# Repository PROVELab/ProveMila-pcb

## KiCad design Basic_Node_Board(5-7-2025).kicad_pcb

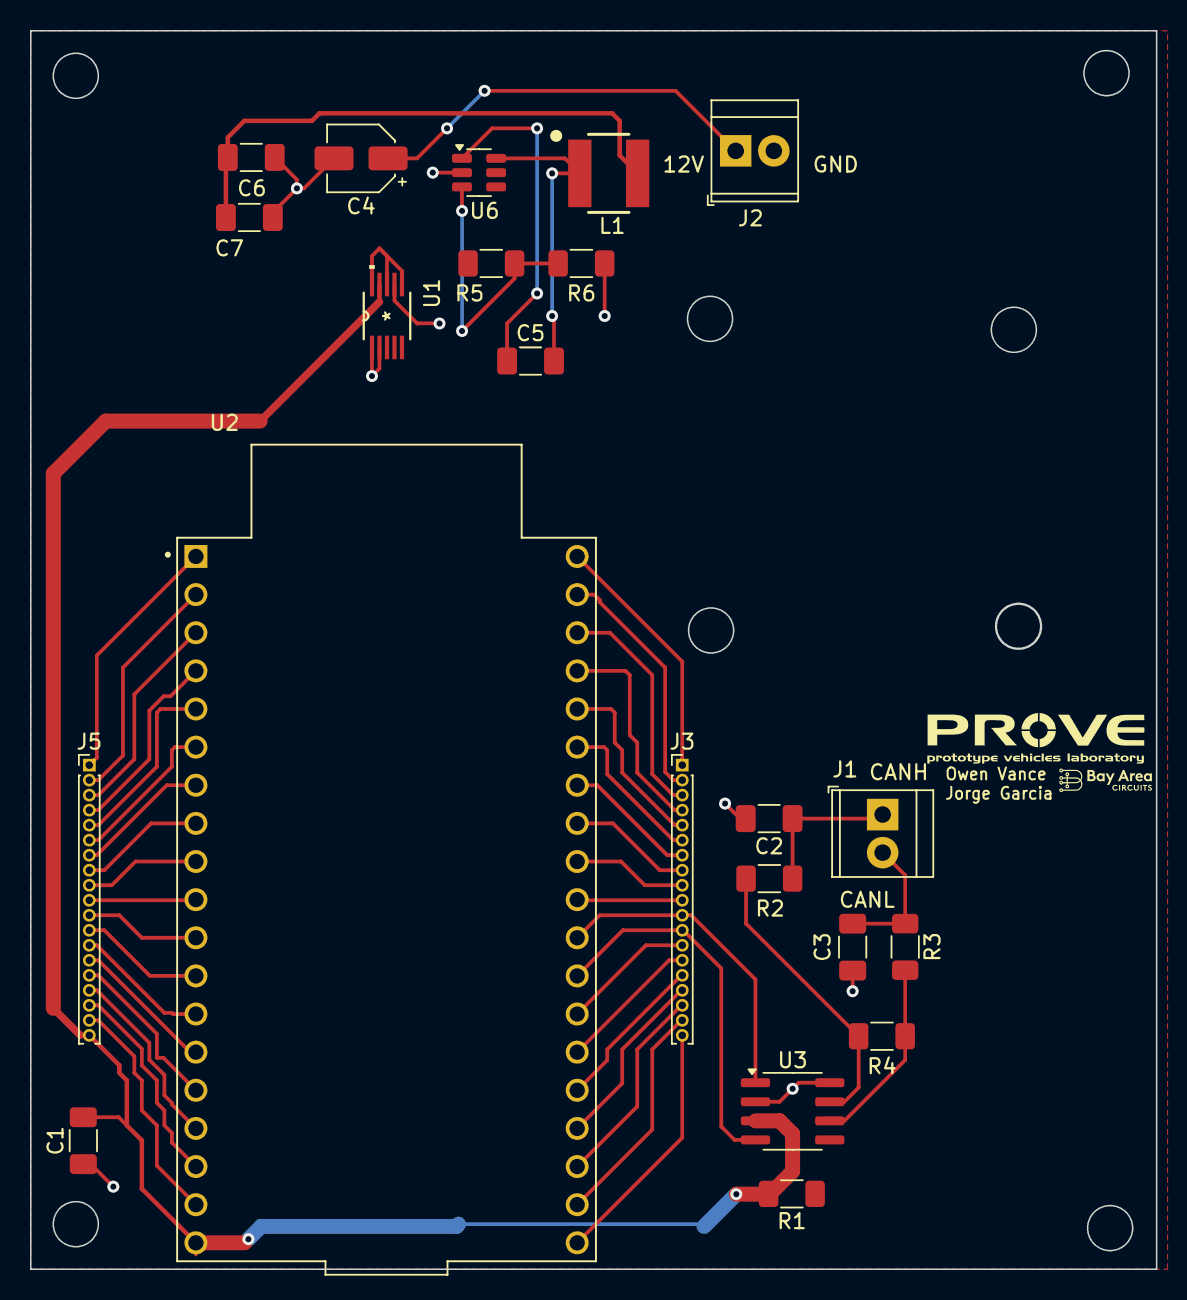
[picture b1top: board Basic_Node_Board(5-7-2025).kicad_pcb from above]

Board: 2 copper layers, 75.0 x 82.5 mm, 22 parts (0 on the bottom side), 48 nets.

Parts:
C1, C5: 0.1u; C_1206_3216Metric_Pad1.33x1.80mm_HandSolder
C2, C3: 30p; C_1206_3216Metric_Pad1.33x1.80mm_HandSolder
C4: 2.2u; CP_Elec_4x5.4
C6, C7: 10u; C_1206_3216Metric_Pad1.33x1.80mm_HandSolder
J1: Conn_01x02_Pin; TerminalBlock_TE_282834-2_1x02_P2.54mm_Horizontal
J2: Conn_01x02; TerminalBlock_TE_282834-2_1x02_P2.54mm_Horizontal
J3, J5: Conn_01x19_Socket; PinHeader_1x19_P1.00mm_Vertical
L1: 10u; WE-LQS_5040
R1: 30m; R_1206_3216Metric_Pad1.30x1.75mm_HandSolder
R2, R3: 0; R_1206_3216Metric_Pad1.30x1.75mm_HandSolder
R4: 120; R_1206_3216Metric_Pad1.30x1.75mm_HandSolder
R5: 115k; R_1206_3216Metric_Pad1.30x1.75mm_HandSolder
R6: 22.1k; R_1206_3216Metric_Pad1.30x1.75mm_HandSolder
U1: INA220 Current Monitor; DGS10
U2: ESP32-DEVKIT-C; MODULE_ESP32-DEVKITC
U3: TJA1050T/CM,118; SOIC-8_3.9x4.9mm_P1.27mm
U6: AP64060WU-7; TSOT-23-6

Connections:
+5V: R1.1, R5.1, U1.6 (VS), U1.8 (VBUS), U1.10 (VIN+)
+5VD: C1.2, J5.19, R1.2, U1.9 (VIN-), U2.19 (EXT_5V), U3.3 (VCC)
/Microcontroller/BUCK_5V: C6.1, C7.1, L1.2
/Microcontroller/CANH: C2.1, J1.1, R2.1
/Microcontroller/CANL: C3.1, J1.2, R3.1
/Power_Supply/12V_IN: C4.1, J2.1
GND: C1.1, C2.2, C3.2, C4.2, C6.2, C7.2, J2.2, J5.14, R6.2, U1.1 (A1), U1.2 (A0), U1.7 (GND), U2.14 (GND1), U3.2 (GND), U3.8 (S), U6.2 (GND)
unnamed: J3.1, U2.38 (GND3)
unnamed: J3.2, U2.37 (IO23)
unnamed: J3.3, U2.36 (IO22)
unnamed: J3.4, U2.35 (TXD0)
unnamed: J3.5, U2.34 (RXD0)
unnamed: J3.6, U2.33 (IO21)
unnamed: J3.7, U2.32 (GND2)
unnamed: J3.8, U2.31 (IO19)
unnamed: J3.9, U2.30 (IO18)
unnamed: J3.10, U2.29 (IO5)
unnamed: J3.11, U2.28 (IO17), U3.1 (TXD)
unnamed: J3.12, U2.27 (IO16), U3.4 (RXD)
unnamed: J3.13, U2.26 (IO4)
unnamed: J3.14, U2.25 (IO0)
unnamed: J3.15, U2.24 (IO2)
unnamed: J3.16, U2.23 (IO15)
unnamed: J3.17, U2.22 (SD1)
unnamed: J3.18, U2.21 (SD0)
unnamed: J3.19, U2.20 (CLK)
unnamed: J5.1, U2.1 (3V3)
unnamed: J5.2, U2.2 (EN)
unnamed: J5.3, U2.3 (SENSOR_VP)
unnamed: J5.4, U2.4 (SENSOR_VN)
unnamed: J5.5, U2.5 (IO34)
unnamed: J5.6, U2.6 (IO35)
unnamed: J5.7, U2.7 (IO32)
unnamed: J5.8, U2.8 (IO33)
unnamed: J5.9, U2.9 (IO25)
unnamed: J5.10, U2.10 (IO26)
unnamed: J5.11, U2.11 (IO27)
unnamed: J5.12, U2.12 (IO14)
unnamed: J5.13, U2.13 (IO12)
unnamed: J5.15, U2.15 (IO13)
unnamed: J5.16, U2.16 (SD2)
unnamed: J5.17, U2.17 (SD3)
unnamed: J5.18, U2.18 (CMD)
unnamed: R2.2, R4.1, U3.7 (CANH)
unnamed: R3.2, R4.2, U3.6 (CANL)
unnamed: C5.1, U6.1 (BST)
unnamed: R5.2, R6.1, U6.3 (FB)
unnamed: C5.2, L1.1, U6.6 (SW)

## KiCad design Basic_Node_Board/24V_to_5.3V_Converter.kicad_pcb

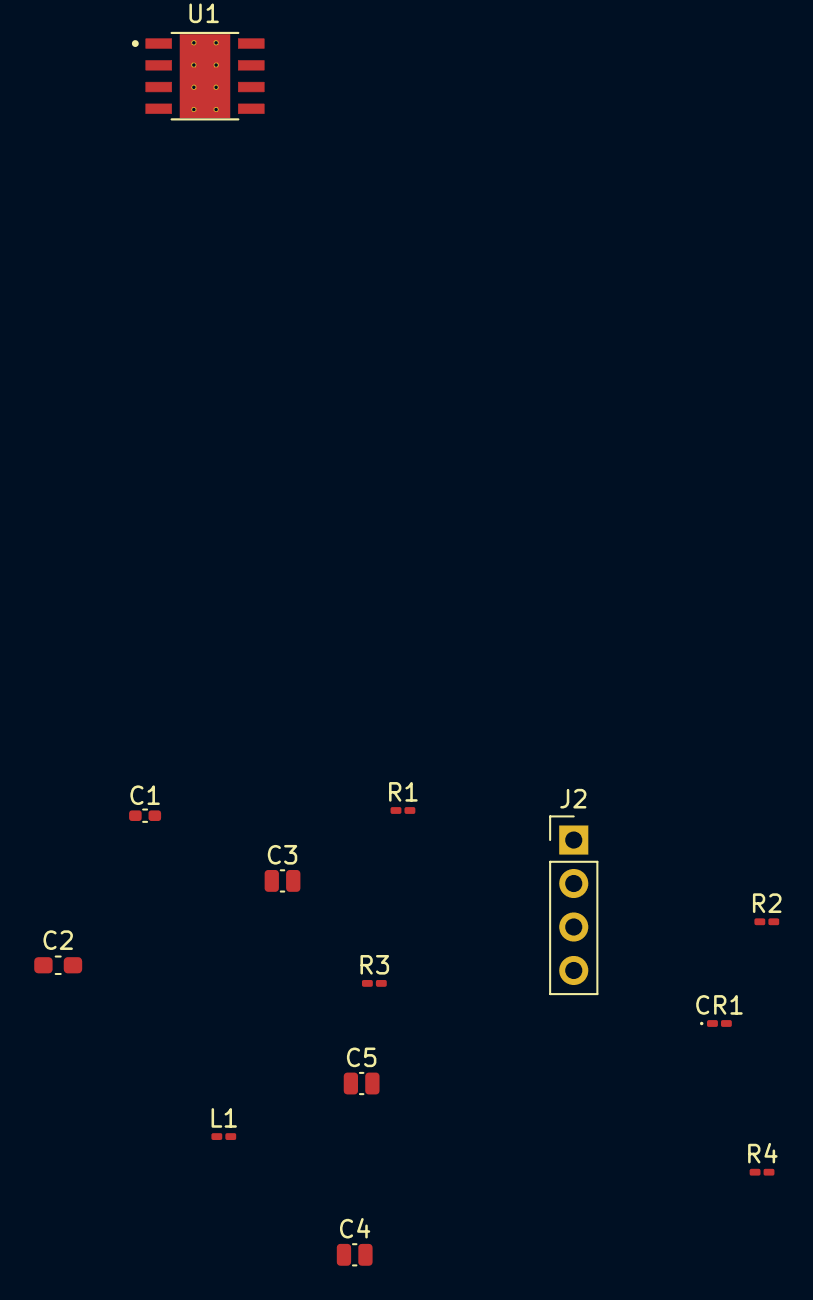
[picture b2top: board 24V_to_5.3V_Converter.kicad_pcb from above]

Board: 2 copper layers, 13 parts (0 on the bottom side), 9 nets, no tracks yet.

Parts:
C1: 10TPE47MAZB; C_0402_1005Metric_Pad0.74x0.62mm_HandSolder
C2: CL05C110JB5NNNC; C_0603_1608Metric_Pad1.08x0.95mm_HandSolder
C3: C0805C122J5GACTU; C_0504_1310Metric_Pad0.83x1.28mm_HandSolder
C4: GRM31CR71H475KA12L; C_0504_1310Metric_Pad0.83x1.28mm_HandSolder
C5: 08053C104KAT2A; C_0504_1310Metric_Pad0.83x1.28mm_HandSolder
CR1: B560C-13-F; D_0201_0603Metric_Pad0.64x0.40mm_HandSolder
J2: Conn_01x02; PinHeader_1x04_P2.54mm_Vertical
L1: SRN8040-100M; L_0201_0603Metric_Pad0.64x0.40mm_HandSolder
R1: CRCW040261K9FKED; R_0201_0603Metric_Pad0.64x0.40mm_HandSolder
R2: CRCW040211K0FKED; R_0201_0603Metric_Pad0.64x0.40mm_HandSolder
R3: CRCW0402118KFKED; R_0201_0603Metric_Pad0.64x0.40mm_HandSolder
R4: RC0201FR-0723K7L; R_0201_0603Metric_Pad0.64x0.40mm_HandSolder
U1: TPS54560BQDDARQ1; VREG_LM5017MR_NOPB

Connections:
5.3V OUT: C1.1, L1.1, R1.1
/24V: C4.2, J2.1, U1.2 (VIN)
GND: C1.2, C2.2, C3.1, C4.1, CR1.2, J2.2, R2.1, R3.1, U1.7 (GND)
unnamed: C3.2, R4.1
unnamed: C5.2, U1.1 (BOOT)
unnamed: C2.1, R4.2, U1.6 (COMP)
unnamed: R1.2, R2.2, U1.5 (FB)
unnamed: R3.2, U1.4 (RT/CLK)
unnamed: C5.1, CR1.1, L1.2, U1.8 (SW)

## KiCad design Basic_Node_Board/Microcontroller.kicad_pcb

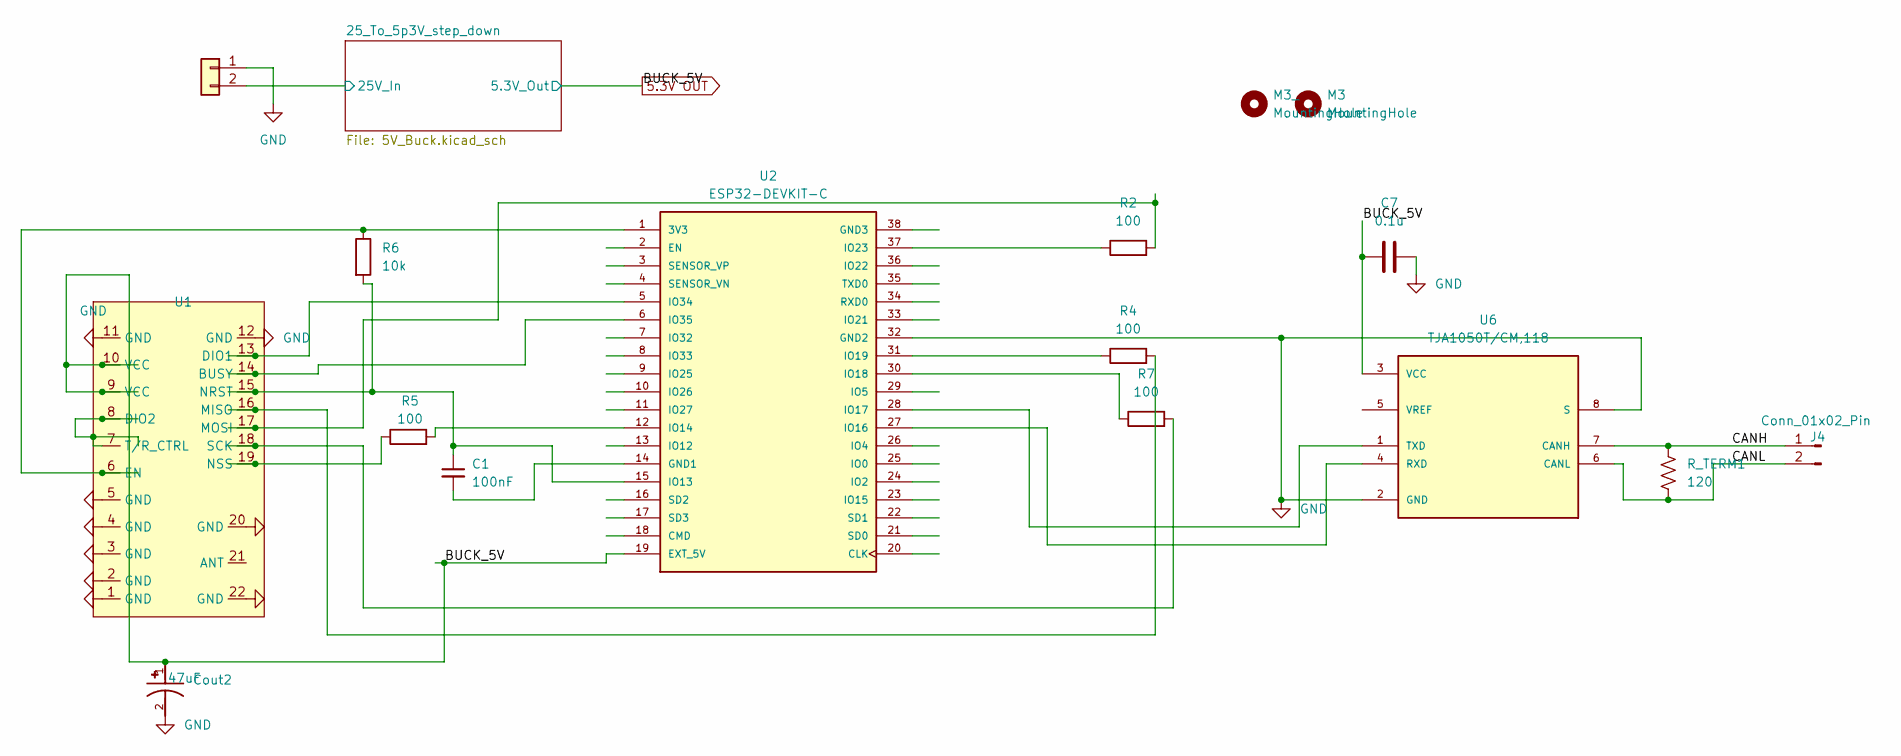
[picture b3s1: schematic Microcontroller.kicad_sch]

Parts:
C1: 100nF; C_1206_3216Metric_Pad1.33x1.80mm_HandSolder
C7: 0.1u; C_1206_3216Metric_Pad1.33x1.80mm_HandSolder; MPN 1206B104K500CT
Cout2: 47uF; CP_EIA-3528-21_Kemet-B_HandSolder
J1: Conn_01x02; TE_1877285-2
J4: Conn_01x02_Pin; TE_1877285-2
M3, M3_: MountingHole; MountingHole_3.2mm_M3
R2, R4, R5, R7: 100; R_1206_3216Metric_Pad1.30x1.75mm_HandSolder
R6: 10k; R_1206_3216Metric_Pad1.30x1.75mm_HandSolder
R_TERM1: 120; R_1206_3216Metric_Pad1.30x1.75mm_HandSolder; MPN RMCF1206JT120R
U1: E22P-915M30S
U2: ESP32-DEVKIT-C; MODULE_ESP32-DEVKITC; PARTREV N/A
U6: TJA1050T/CM,118; SOIC-8_3.9x4.9mm_P1.27mm; PARTREV 4

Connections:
5.3V OUT: C7.2, Cout2.1, U1.9 (VCC), U1.10 (VCC), U2.19 (EXT_5V), U6.3 (VCC); also elsewhere on the board
/25_To_5p3V_step_down/25V_In: J1.2; also elsewhere on the board
/CANH: J4.1, R_TERM1.1, U6.7 (CANH)
/CANL: J4.2, R_TERM1.2, U6.6 (CANL)
GND: C7.1, Cout2.2, J1.1, U1.1 (GND), U1.2 (GND), U1.3 (GND), U1.4 (GND), U1.5 (GND), U1.11 (GND), U1.12 (GND), U1.20 (GND), U1.22 (GND), U2.32 (GND2), U6.2 (GND), U6.8 (S); also elsewhere on the board
unnamed: U1.14 (BUSY), U2.6 (IO35)
unnamed: U1.13 (DIO1), U2.5 (IO34)
unnamed: U1.7 (T/R_CTRL), U1.8 (DIO2)
unnamed: R6.1, U1.6 (EN), U2.1 (3V3)
unnamed: R4.2, U1.16 (MISO)
unnamed: R2.2, U1.17 (MOSI)
unnamed: C1.1, R6.2, U1.15 (NRST), U2.15 (IO13)
unnamed: R5.1, U1.19 (NSS)
unnamed: R7.2, U1.18 (SCK)
unnamed: C1.2, U2.14 (GND1)
unnamed: R5.2, U2.12 (IO14)
unnamed: U2.27 (IO16), U6.4 (RXD)
unnamed: U2.28 (IO17), U6.1 (TXD)
unnamed: R7.1, U2.30 (IO18)
unnamed: R4.1, U2.31 (IO19)
unnamed: R2.1, U2.37 (IO23)

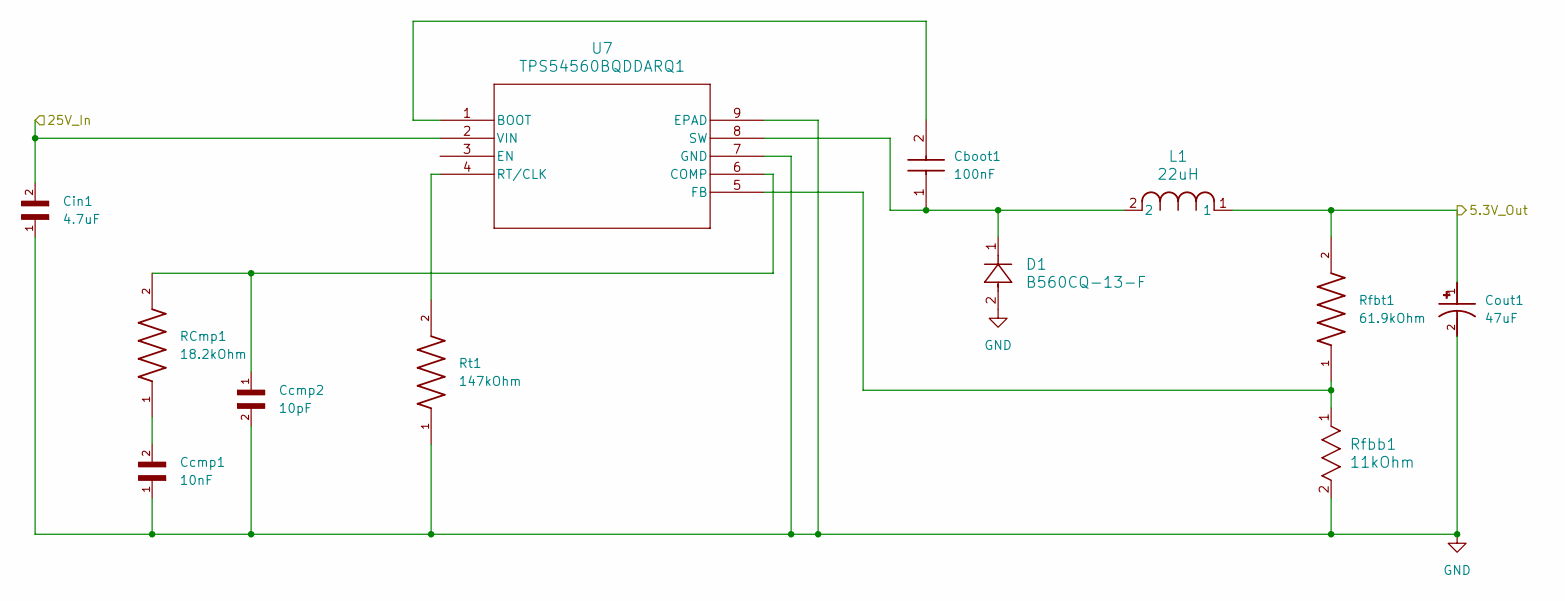
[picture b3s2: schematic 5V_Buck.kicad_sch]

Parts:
Cboot1: 100nF; C_1206_3216Metric_Pad1.33x1.80mm_HandSolder
Ccmp1: 10nF; C_1206_3216Metric_Pad1.33x1.80mm_HandSolder
Ccmp2: 10pF; C_1206_3216Metric_Pad1.33x1.80mm_HandSolder
Cin1: 4.7uF; C_1206_3216Metric_Pad1.33x1.80mm_HandSolder
Cout1: 47uF; CP_EIA-3528-21_Kemet-B_HandSolder
D1: B560CQ-13-F; D_SMC
L1: 22uH; L_Bourns_SRP1245A
RCmp1: 18.2kOhm; R_1206_3216Metric_Pad1.30x1.75mm_HandSolder
Rfbb1: 11kOhm; R_1206_3216Metric_Pad1.30x1.75mm_HandSolder
Rfbt1: 61.9kOhm; R_1206_3216Metric_Pad1.30x1.75mm_HandSolder
Rt1: 147kOhm; R_1206_3216Metric_Pad1.30x1.75mm_HandSolder
U7: TPS54560BQDDARQ1; SOIC-8-1EP_3.9x4.9mm_P1.27mm_EP2.29x3mm

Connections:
5.3V OUT: Cout1.1, L1.1, Rfbt1.2; also elsewhere on the board
/25_To_5p3V_step_down/25V_In: Cin1.2, U7.2 (VIN); also elsewhere on the board
GND: Ccmp1.1, Ccmp2.2, Cin1.1, Cout1.2, D1.2, Rfbb1.2, Rt1.1, U7.7 (GND), U7.9 (EPAD); also elsewhere on the board
unnamed: Ccmp1.2, RCmp1.1
unnamed: Cboot1.2, U7.1 (BOOT)
unnamed: Ccmp2.1, RCmp1.2, U7.6 (COMP)
unnamed: Rfbb1.1, Rfbt1.1, U7.5 (FB)
unnamed: Rt1.2, U7.4 (RT/CLK)
unnamed: Cboot1.1, D1.1, L1.2, U7.8 (SW)

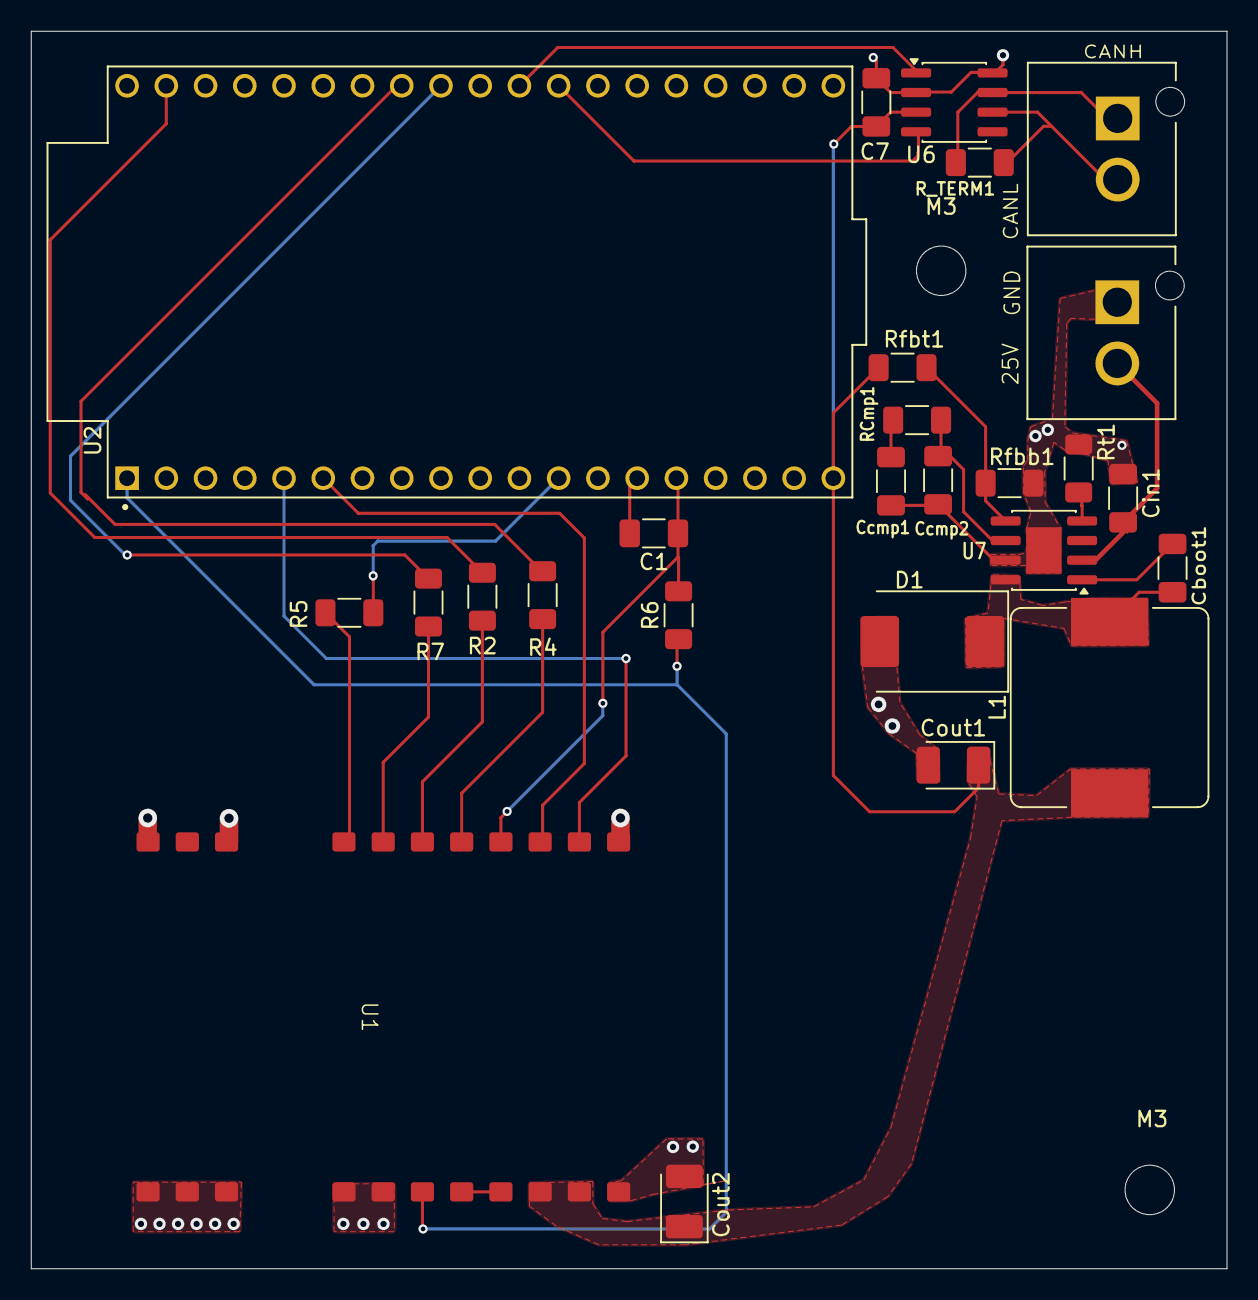
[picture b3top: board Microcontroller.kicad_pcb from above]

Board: 4 copper layers, 77.4 x 80.1 mm, 28 parts (0 on the bottom side), 27 nets.

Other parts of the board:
M3_1: MountingHole; MountingHole_3.2mm_M3

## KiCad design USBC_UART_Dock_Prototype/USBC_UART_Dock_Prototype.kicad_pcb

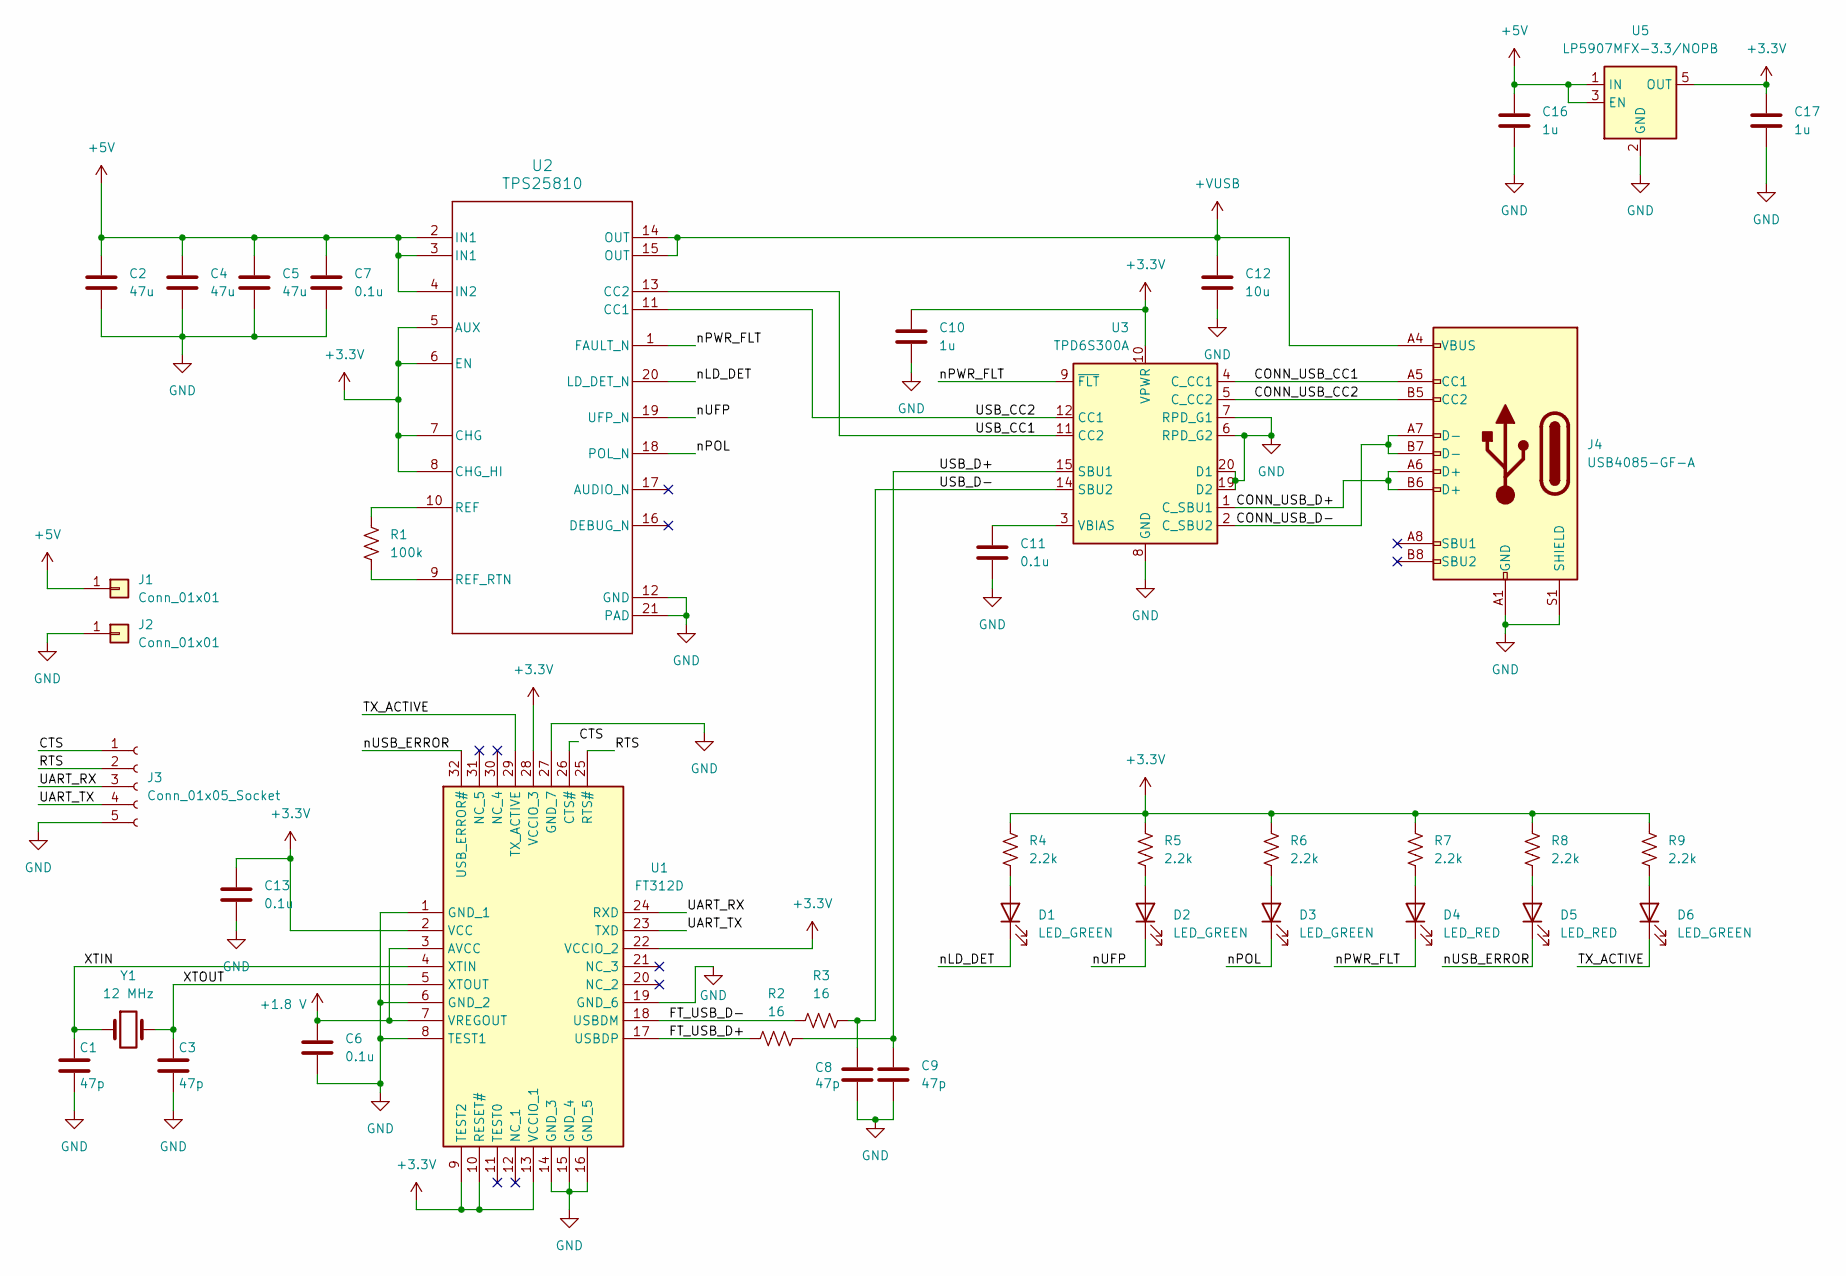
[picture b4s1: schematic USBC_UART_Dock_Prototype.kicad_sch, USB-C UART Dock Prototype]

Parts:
C1, C3, C8, C9: 47p; C_1206_3216Metric_Pad1.33x1.80mm_HandSolder; MPN 885012008003
C2, C4, C5: 47u; C_1206_3216Metric_Pad1.33x1.80mm_HandSolder; MPN CL31A476MQHNNWE
C6, C7, C11, C13: 0.1u; C_0603_1608Metric_Pad1.08x0.95mm_HandSolder; MPN GRM188R71H104KA93D
C10, C16, C17: 1u; C_1206_3216Metric_Pad1.33x1.80mm_HandSolder; MPN 885012208013
C12: 10u; C_1206_3216Metric_Pad1.33x1.80mm_HandSolder; MPN CL31A106KPHNNNE
D1, D2, D3, D6: LED_GREEN; LED_0805_2012Metric_Pad1.15x1.40mm_HandSolder; MPN 150080GS75000
D4, D5: LED_RED; LED_0805_2012Metric_Pad1.15x1.40mm_HandSolder; MPN 150080RS75000
J1, J2: Conn_01x01; Banana_Jack_1Pin
J3: Conn_01x05_Socket; PinSocket_1x05_P2.54mm_Vertical
J4: USB4085-GF-A; USB_C_Receptacle_GCT_USB4085; MPN USB4085-GF-A
R1: 100k; R_1206_3216Metric_Pad1.30x1.75mm_HandSolder; MPN RC1206FR-07100KL
R2, R3: 16; R_1206_3216Metric_Pad1.30x1.75mm_HandSolder; MPN RC1206FR-0716RL
R4, R5, R6, R7, R8, R9: 2.2k; R_1206_3216Metric_Pad1.30x1.75mm_HandSolder; MPN RMCF1206JT2K20
U1: FT312D; LQFP-32_7x7mm_P0.8mm; Manufacturer_Part_Number FT312D-32L1C-R; Mouser Part Number 895-FT312D-32L1C-R
U2: TPS25810; WQFN-20-3x4mm; MPN TPS25810RVCT
U3: TPD6S300A; WQFN-20-1EP_3x3mm_P0.4mm_EP1.7x1.7mm_ThermalVias; MPN TPD6S300ARUKR
U5: LP5907MFX-3.3/NOPB; SOT-23-5_HandSoldering; MPN LP5907MFX-3.3/NOPB
Y1: 12 MHz; Crystal_SMD_HC49-SD; MPN J49SML-F-G-G-K-12M0

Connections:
+1.8 V: C6.1, U1.3 (AVCC), U1.7 (VREGOUT)
+3.3V: C10.1, C13.1, C17.1, R4.1, R5.1, R6.1, R7.1, R8.1, R9.1, U1.2 (VCC), U1.9 (TEST2), U1.10 (RESET#), U1.13 (VCCIO_1), U1.22 (VCCIO_2), U1.28 (VCCIO_3), U2.5 (AUX), U2.6 (EN), U2.7 (CHG), U2.8 (CHG_HI), U3.10 (VPWR), U5.5 (OUT)
+5V: C2.1, C4.1, C5.1, C7.1, C16.1, J1.1, U2.2 (IN1), U2.3 (IN1), U2.4 (IN2), U5.1 (IN), U5.3 (EN)
+VUSB: C12.1, J4.A4 (VBUS), J4.A9 (VBUS), J4.B4 (VBUS), J4.B9 (VBUS), U2.14 (OUT), U2.15 (OUT)
/CONN_USB_CC1: J4.A5 (CC1), U3.4 (C_CC1)
/CONN_USB_CC2: J4.B5 (CC2), U3.5 (C_CC2)
/CONN_USB_D+: J4.A6 (D+), J4.B6 (D+), U3.1 (C_SBU1)
/CONN_USB_D-: J4.A7 (D-), J4.B7 (D-), U3.2 (C_SBU2)
/CTS: J3.1, U1.26 (CTS#)
/FT_USB_D+: R2.1, U1.17 (USBDP)
/FT_USB_D-: R3.1, U1.18 (USBDM)
/RTS: J3.2, U1.25 (RTS#)
/TX_ACTIVE: D6.1 (K), U1.29 (TX_ACTIVE)
/UART_RX: J3.3, U1.24 (RXD)
/UART_TX: J3.4, U1.23 (TXD)
/USB_CC1: U2.13 (CC2), U3.11 (CC2)
/USB_CC2: U2.11 (CC1), U3.12 (CC1)
/USB_D+: C9.1, R2.2, U3.15 (SBU1)
/USB_D-: C8.1, R3.2, U3.14 (SBU2)
/XTIN: C1.1, U1.4 (XTIN), Y1.1
/XTOUT: C3.1, U1.5 (XTOUT), Y1.2
/nLD_DET: D1.1 (K), U2.20 (LD_DET_N)
/nPOL: D3.1 (K), U2.18 (POL_N)
/nPWR_FLT: D4.1 (K), U2.1 (FAULT_N), U3.9 (~FLT)
/nUFP: D2.1 (K), U2.19 (UFP_N)
/nUSB_ERROR: D5.1 (K), U1.32 (USB_ERROR#)
GND: C1.2, C2.2, C3.2, C4.2, C5.2, C6.2, C7.2, C8.2, C9.2, C10.2, C11.2, C12.2, C13.2, C16.2, C17.2, J2.1, J3.5, J4.A1 (GND), J4.A12 (GND), J4.B1 (GND), J4.B12 (GND), J4.S1 (SHIELD), U1.1 (GND_1), U1.6 (GND_2), U1.8 (TEST1), U1.14 (GND_3), U1.15 (GND_4), U1.16 (GND_5), U1.19 (GND_6), U1.27 (GND_7), U2.12 (GND), U2.21 (PAD), U2.V, U3.6 (RPD_G2), U3.7 (RPD_G1), U3.8 (GND), U3.13 (GND), U3.16 (GND), U3.17 (GND), U3.18 (GND), U3.19 (D2), U3.20 (D1), U3.21 (GND), U5.2 (GND)
unnamed: D1.2 (A), R4.2
unnamed: D2.2 (A), R5.2
unnamed: D3.2 (A), R6.2
unnamed: D4.2 (A), R7.2
unnamed: D5.2 (A), R8.2
unnamed: D6.2 (A), R9.2
unnamed: R1.1, U2.10 (REF)
unnamed: R1.2, U2.9 (REF_RTN)
unnamed: C11.1, U3.3 (VBIAS)

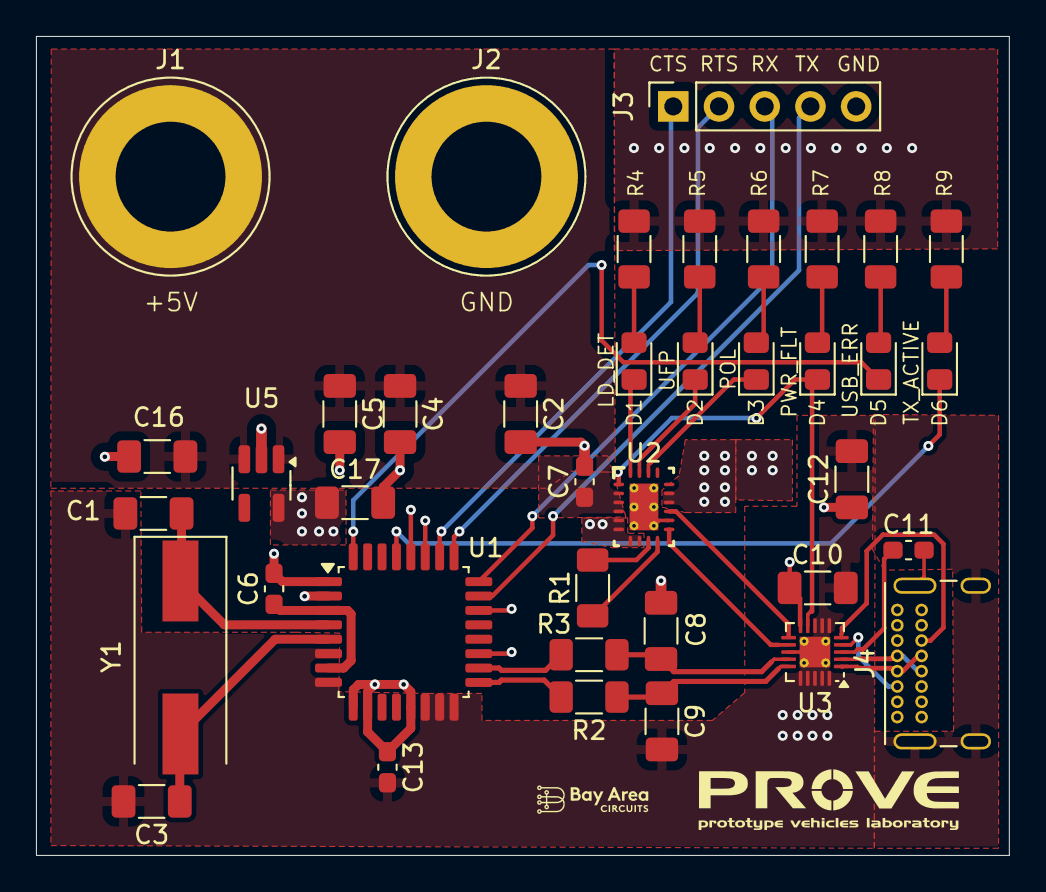
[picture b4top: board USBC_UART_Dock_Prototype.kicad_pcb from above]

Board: 4 copper layers, 54.1 x 45.5 mm, 39 parts (0 on the bottom side), 36 nets.
